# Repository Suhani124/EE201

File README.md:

# EE201

Hi, I'm Suhani. I'm a junior in ECE interested in neural engineering and machine learning.

This quarter I'm taking:
1. EE 201
2. EE 271
3. EE 280
4. CSE 373
5. MUSIC 116

Outside of classes, I like to watch crime tv shows, bike, read, and swim.

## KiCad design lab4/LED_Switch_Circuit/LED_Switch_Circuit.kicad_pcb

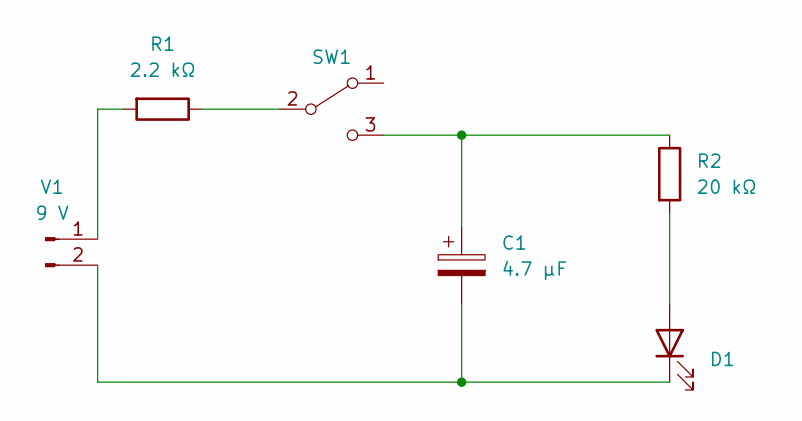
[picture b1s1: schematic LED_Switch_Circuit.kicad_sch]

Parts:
C1: 4.7 μF; C_Radial_D5.0mm_H5.0mm_P2.00mm
D1: LED; LED_D5.0mm
R1: 2.2 kΩ; R_Axial_DIN0516_L15.5mm_D5.0mm_P20.32mm_Horizontal
R2: 20 kΩ; R_Axial_DIN0516_L15.5mm_D5.0mm_P20.32mm_Horizontal
SW1: SW_SPDT; SW_E-Switch_EG1224_SPDT_Angled
V1: 9 V; JST_PH_B2B-PH-K_1x02_P2.00mm_Vertical

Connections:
unnamed: C1.1, R2.1, SW1.3 (C)
unnamed: C1.2, D1.1 (K), V1.2
unnamed: D1.2 (A), R2.2
unnamed: R1.1, SW1.2 (B)
unnamed: R1.2, V1.1

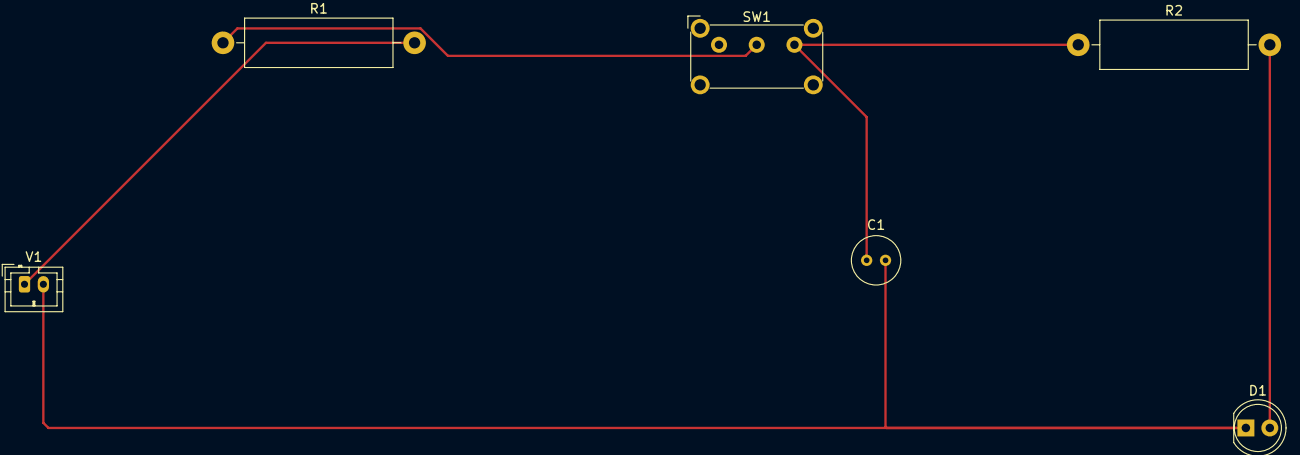
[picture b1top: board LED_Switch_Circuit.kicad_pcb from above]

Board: 2 copper layers, 6 parts (0 on the bottom side), 5 nets.

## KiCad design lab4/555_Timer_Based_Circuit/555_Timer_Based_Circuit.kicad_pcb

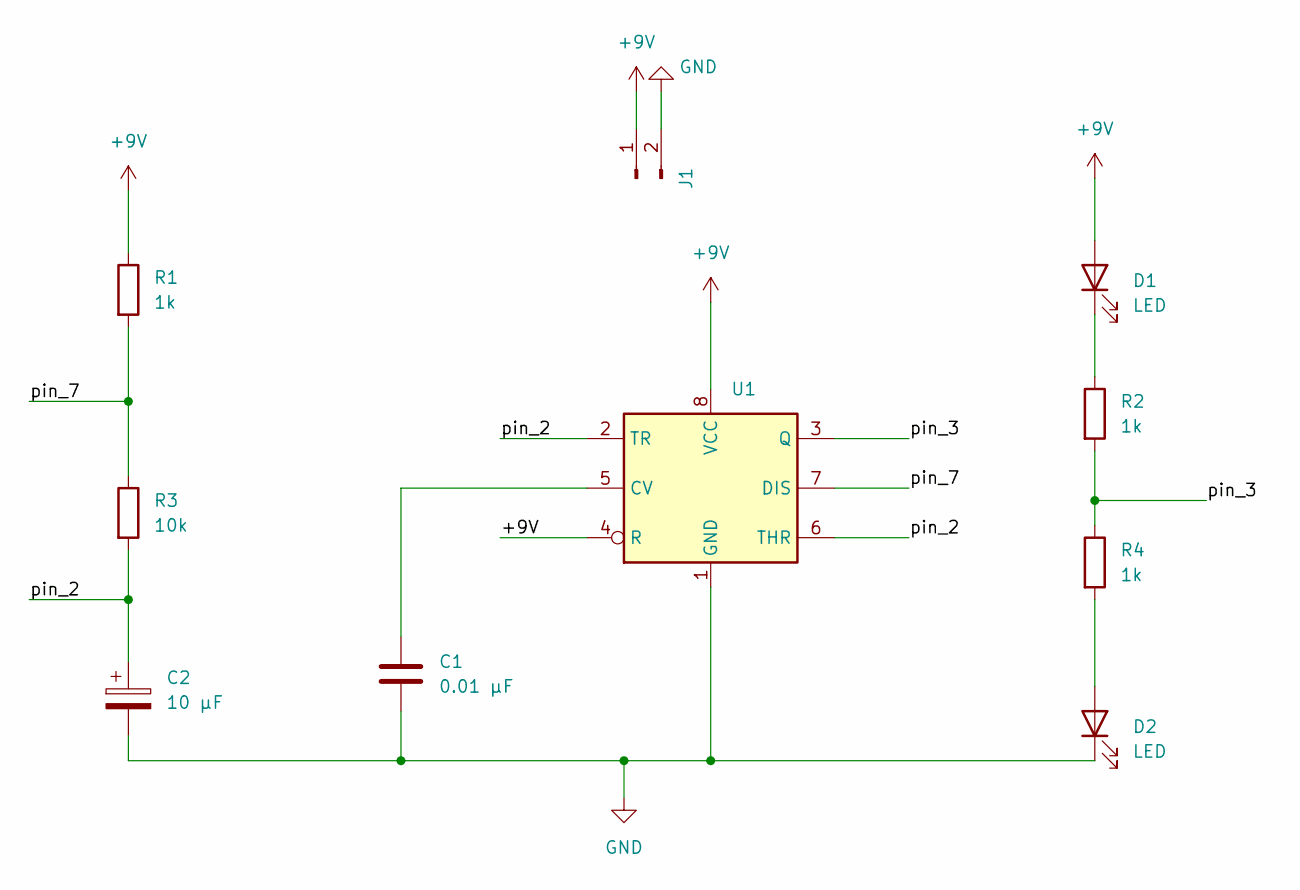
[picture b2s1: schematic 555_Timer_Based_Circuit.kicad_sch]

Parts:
C1: 0.01 μF; C_0805_2012Metric_Pad1.18x1.45mm_HandSolder
C2: 10 μF; CP_EIA-3216-18_Kemet-A_Pad1.58x1.35mm_HandSolder
D1, D2: LED; LED_1206_3216Metric_Pad1.42x1.75mm_HandSolder
J1: J1; TerminalBlock_bornier-2_P5.08mm
R1, R2, R4: 1k; R_0805_2012Metric_Pad1.20x1.40mm_HandSolder
R3: 10k; R_0805_2012Metric_Pad1.20x1.40mm_HandSolder
U1: NE555D; SOIC-8-1EP_3.9x4.9mm_P1.27mm_EP2.29x3mm

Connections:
+9V: D1.2 (A), J1.1, R1.1, U1.4 (R), U1.8 (VCC)
/pin_2: C2.1, R3.2, U1.2 (TR), U1.6 (THR)
/pin_3: R2.2, R4.1, U1.3 (Q)
/pin_7: R1.2, R3.1, U1.7 (DIS)
GND: C1.2, C2.2, D2.1 (K), J1.2, U1.1 (GND)
unnamed: C1.1, U1.5 (CV)
unnamed: D1.1 (K), R2.1
unnamed: D2.2 (A), R4.2

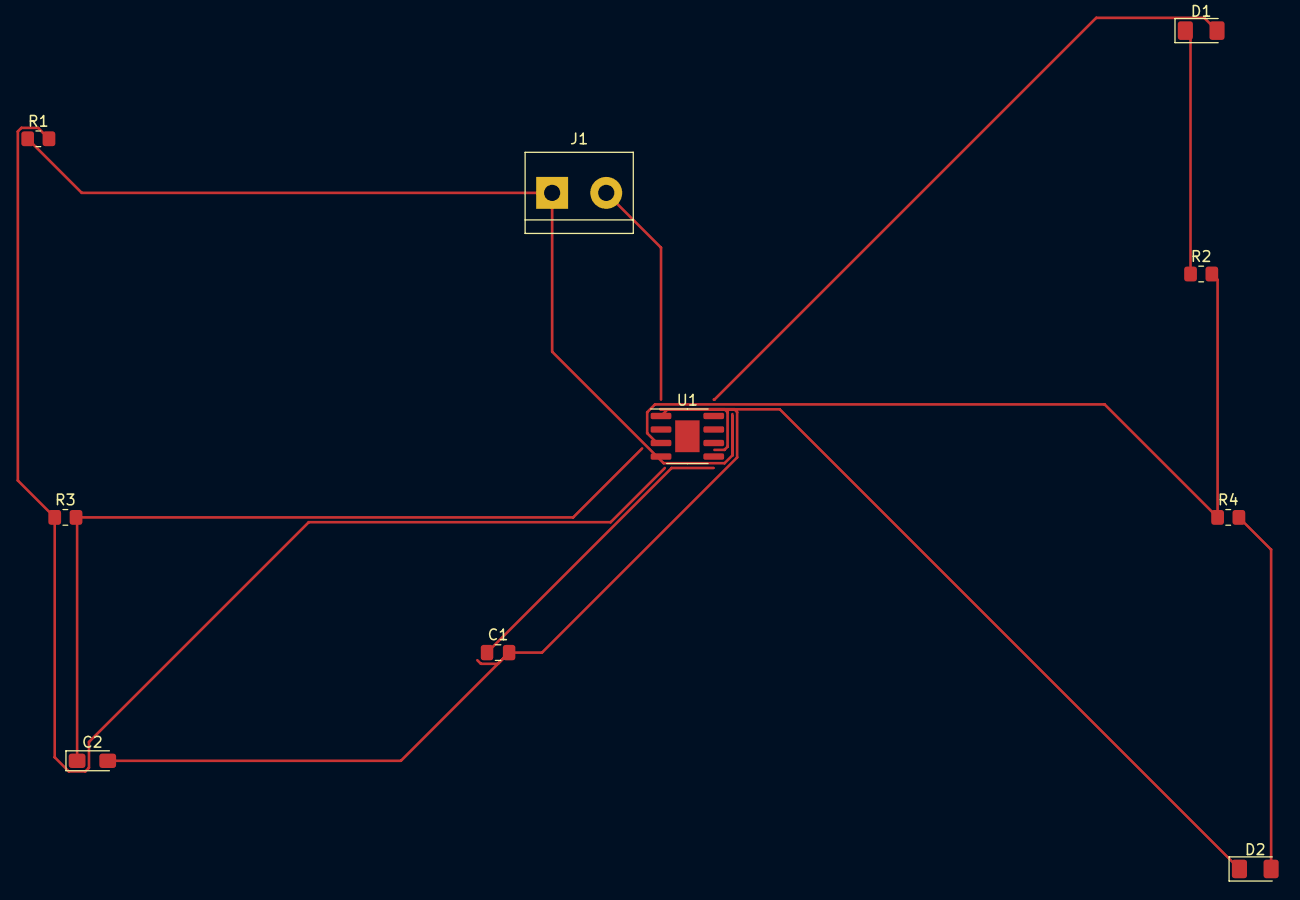
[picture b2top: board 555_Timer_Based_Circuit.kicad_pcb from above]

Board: 2 copper layers, 10 parts (0 on the bottom side), 8 nets.

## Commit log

2023-01-27 Create hi
2023-02-01 Create lab4
